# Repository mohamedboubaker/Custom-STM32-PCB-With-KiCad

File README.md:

# Custom STM32 PCB With KiCad
The design details are posted on EmbeddedProjects101.com: <a href="https://embeddedprojects101.com/custom-stm32-development-board/">Build a Custom STM32 PCB with KiCad</a>

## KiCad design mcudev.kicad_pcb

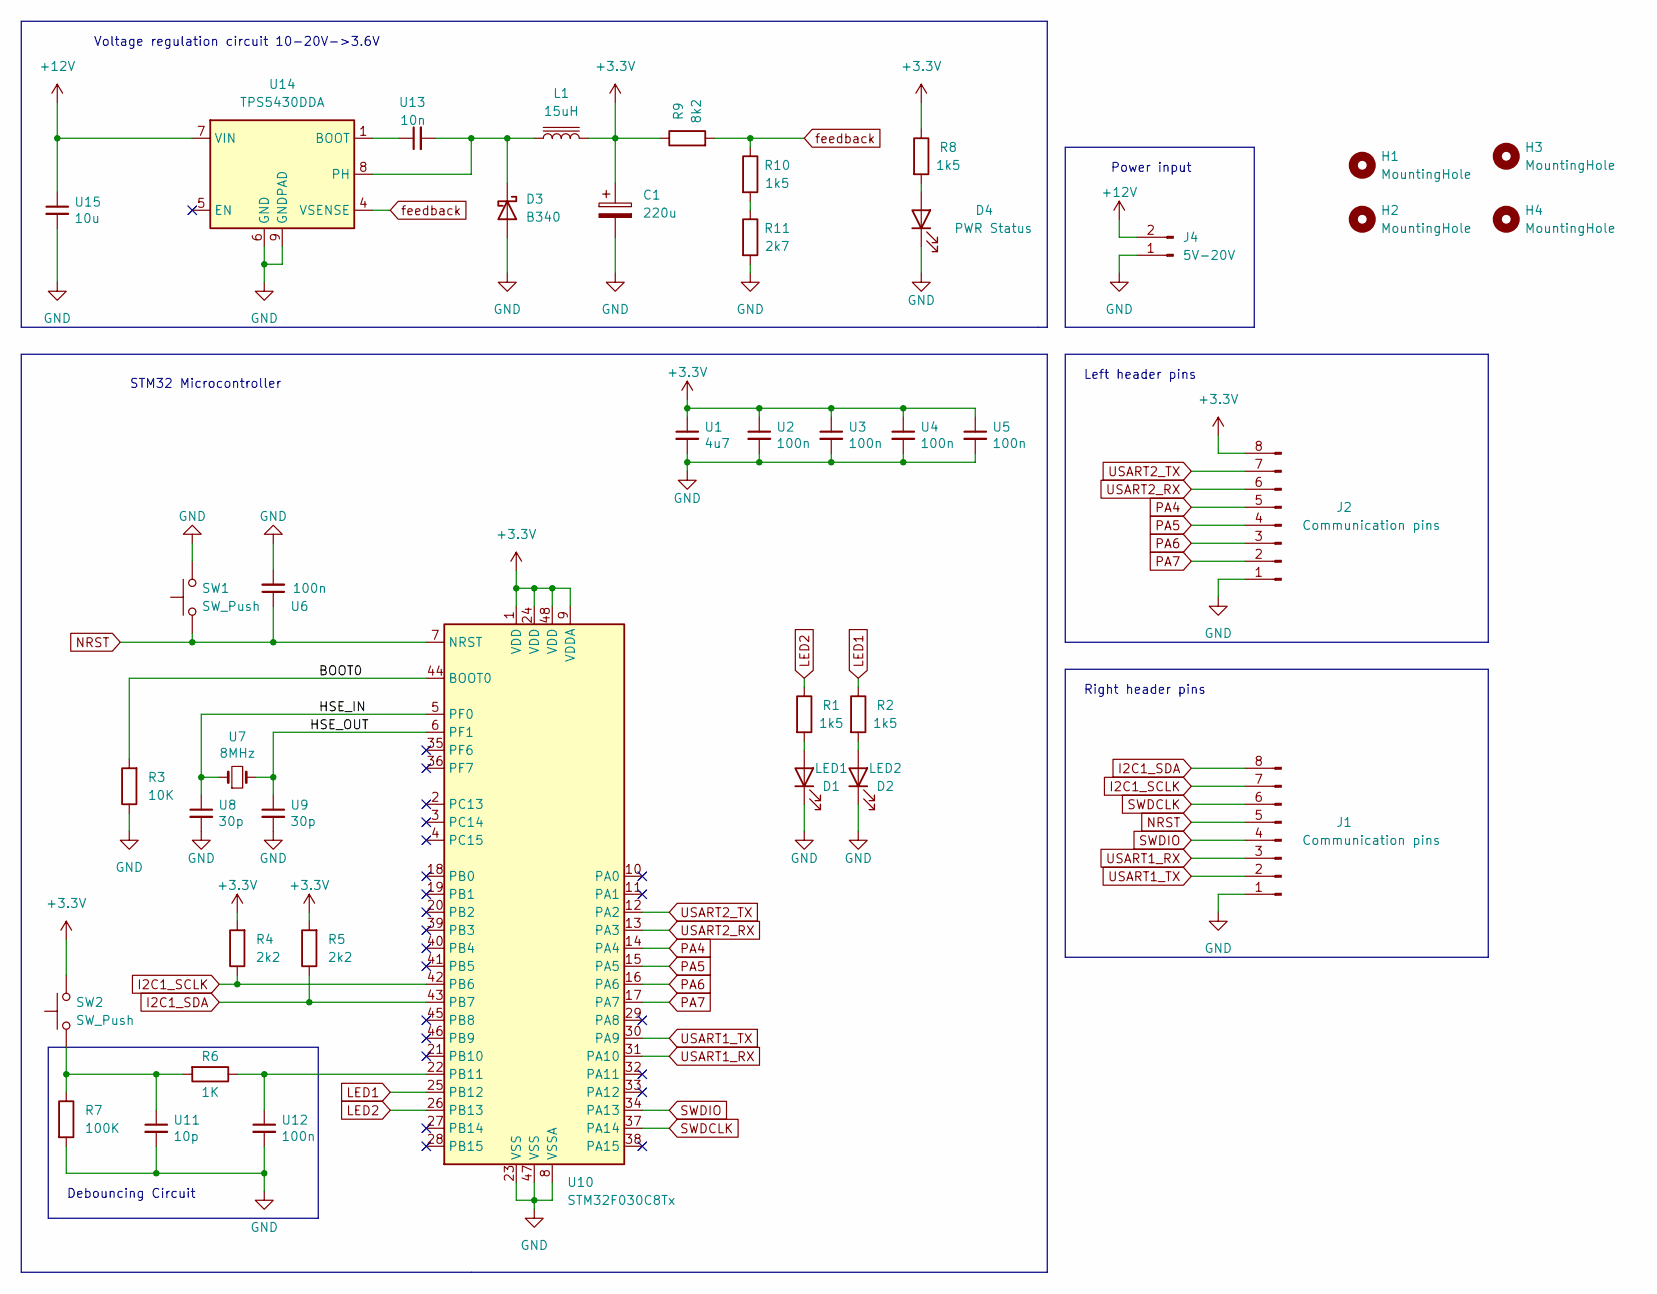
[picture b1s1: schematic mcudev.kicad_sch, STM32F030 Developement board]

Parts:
C1: 220u; CP_EIA-7343-15_Kemet-W; LCSC Part # C242173
D1: LED1; LED_0603_1608Metric; LCSC Part # C72043
D2: LED2; LED_0603_1608Metric; LCSC Part # C72041
D3: B340; D_SMA; LCSC Part # C64982
D4: PWR Status; LED_0603_1608Metric; LCSC Part # C2286
H1, H2, H3, H4: MountingHole; MountingHole_2.2mm_M2
J1, J2: Communication pins; PinHeader_1x08_P2.54mm_Vertical
J4: 5V-20V; PinHeader_1x02_P2.54mm_Vertical
L1: 15uH; L_10.4x10.4_H4.8; LCSC Part # C225048
R1, R2, R8: 1k5; R_0603_1608Metric; LCSC Part # C22843
R3: 10K; R_0402_1005Metric; LCSC Part # C25744
R4, R5: 2k2; R_0402_1005Metric; LCSC Part # C25879
R6: 1K; R_0603_1608Metric; LCSC Part # C21190
R7: 100K; R_0603_1608Metric; LCSC Part # C25803
R9: 8k2; R_0805_2012Metric; LCSC Part # C17828
R10: 1k5; R_0805_2012Metric; LCSC Part # C4310
R11: 2k7; R_0805_2012Metric; LCSC Part # C17530
SW1, SW2: SW_Push; SW_Push_1P1T_NO_CK_KSC6xxJ; LCSC Part # C318884
U1: 4u7; C_0603_1608Metric; LCSC Part # C19666
U2, U3, U4, U5, U6, U12: 100n; C_0402_1005Metric; LCSC Part # C1525
U7: 8MHz; Crystal_SMD_5032-2Pin_5.0x3.2mm; LCSC Part # C115962
U8, U9: 30p; C_0402_1005Metric; LCSC Part # C1570
U10: STM32F030C8Tx; LQFP-48_7x7mm_P0.5mm; LCSC Part # C23922
U11: 10p; C_0402_1005Metric; LCSC Part # C32949
U13: 10n; C_0805_2012Metric; LCSC Part # C1710
U14: TPS5430DDA; TI_SO-PowerPAD-8_ThermalVias; LCSC Part # C9864
U15: 10u; C_0805_2012Metric; LCSC Part # C15850

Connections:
+3.3V: C1.1, J2.8, L1.2, R4.2, R5.2, R8.1, R9.1, SW2.2, U1.1, U2.1, U3.1, U4.1, U5.1, U10.1 (VDD), U10.9 (VDDA), U10.24 (VDD), U10.48 (VDD)
+12V: J4.2, U14.7 (VIN), U15.1
/BOOT0: R3.2, U10.44 (BOOT0)
/HSE_IN: U7.1, U8.1, U10.5 (PF0)
/HSE_OUT: U7.2, U9.1, U10.6 (PF1)
GND: C1.2, D1.1 (K), D2.1 (K), D3.2 (A), D4.1 (K), J1.1, J2.1, J4.1, R3.1, R7.2, R11.2, SW1.2, U1.2, U2.2, U3.2, U4.2, U5.2, U6.2, U8.2, U9.2, U10.8 (VSSA), U10.23 (VSS), U10.47 (VSS), U11.2, U12.2, U14.6 (GND), U14.9 (GNDPAD), U15.2
I2C1_SCLK: J1.7, R4.1, U10.42 (PB6)
I2C1_SDA: J1.8, R5.1, U10.43 (PB7)
LED1: R2.1, U10.25 (PB12)
LED2: R1.1, U10.26 (PB13)
NRST: J1.5, SW1.1, U6.1, U10.7 (NRST)
unnamed: D1.2 (A), R1.2
unnamed: D2.2 (A), R2.2
unnamed: D3.1 (K), L1.1, U13.2, U14.8 (PH)
unnamed: D4.2 (A), R8.2
unnamed: R6.1, U10.22 (PB11), U12.1
unnamed: R6.2, R7.1, SW2.1, U11.1
unnamed: R10.2, R11.1
unnamed: U13.1, U14.1 (BOOT)
PA4: J2.5, U10.14 (PA4)
PA5: J2.4, U10.15 (PA5)
PA6: J2.3, U10.16 (PA6)
PA7: J2.2, U10.17 (PA7)
SWDCLK: J1.6, U10.37 (PA14)
SWDIO: J1.4, U10.34 (PA13)
USART1_RX: J1.3, U10.31 (PA10)
USART1_TX: J1.2, U10.30 (PA9)
USART2_RX: J2.6, U10.13 (PA3)
USART2_TX: J2.7, U10.12 (PA2)
feedback: R9.2, R10.1, U14.4 (VSENSE)

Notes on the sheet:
Power input
STM32 Microcontroller
Voltage regulation circuit 10-20V->3.6V
Right header pins
Debouncing Circuit
Left header pins

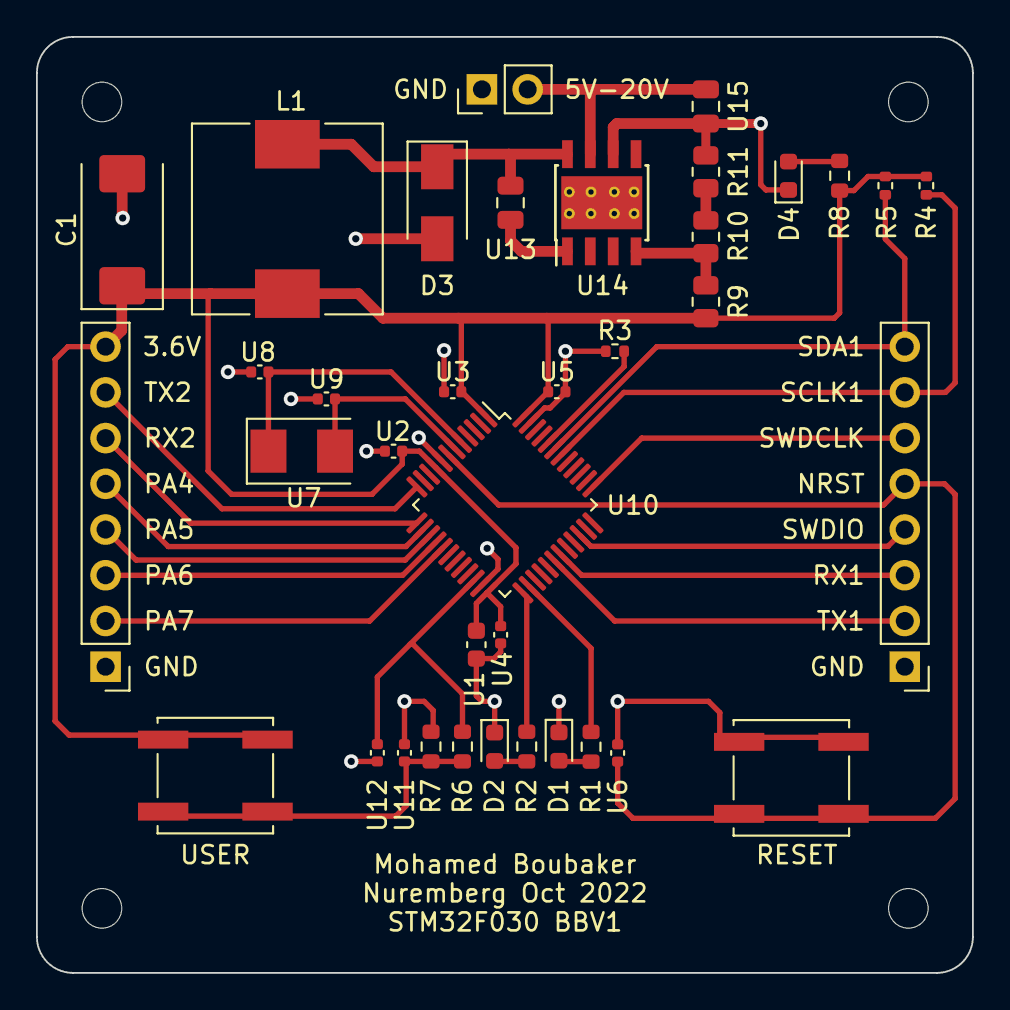
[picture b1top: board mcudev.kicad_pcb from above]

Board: 2 copper layers, 52.0 x 52.0 mm, 41 parts (0 on the bottom side), 30 nets.

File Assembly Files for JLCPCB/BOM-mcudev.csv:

Comment,Designator,Footprint,LCSC
"220u","C1","Capacitor_Tantalum_SMD:CP_EIA-7343-15_Kemet-W","C242173"
"LED1","D1","LED_SMD:LED_0603_1608Metric","C72043"
"LED2","D2","LED_SMD:LED_0603_1608Metric","C72041"
"B340","D3","Diode_SMD:D_SMA","C64982"
"PWR Status","D4","LED_SMD:LED_0603_1608Metric","C2286"
"MountingHole","H1,H2,H3,H4","MountingHole:MountingHole_2.2mm_M2",""
"Communication pins","J1,J2","Connector_PinHeader_2.54mm:PinHeader_1x08_P2.54mm_Vertical",""
"5V-20V","J4","Connector_PinHeader_2.54mm:PinHeader_1x02_P2.54mm_Vertical",""
"15uH","L1","Inductor_SMD:L_10.4x10.4_H4.8","C225048"
"1k5","R1,R2,R8","Resistor_SMD:R_0603_1608Metric","C22843"
"1k5","R10","Resistor_SMD:R_0805_2012Metric","C4310"
"2k7","R11","Resistor_SMD:R_0805_2012Metric","C17530"
"10K","R3","Resistor_SMD:R_0402_1005Metric","C25744"
"2k2","R4,R5","Resistor_SMD:R_0402_1005Metric","C25879"
"1K","R6","Resistor_SMD:R_0603_1608Metric","C21190"
"100K","R7","Resistor_SMD:R_0603_1608Metric","C25803"
"8k2","R9","Resistor_SMD:R_0805_2012Metric","C17828"
"SW_Push","SW1,SW2","Button_Switch_SMD:SW_Push_1P1T_NO_CK_KSC6xxJ","C318884"
"4u7","U1","Capacitor_SMD:C_0603_1608Metric","C19666"
"STM32F030C8Tx","U10","Package_QFP:LQFP-48_7x7mm_P0.5mm","C23922"
"10p","U11","Capacitor_SMD:C_0402_1005Metric","C32949"
"10n","U13","Capacitor_SMD:C_0805_2012Metric","C1710"
"TPS5430DDA","U14","Package_SO:TI_SO-PowerPAD-8_ThermalVias","C9864"
"10u","U15","Capacitor_SMD:C_0805_2012Metric","C15850"
"100n","U2,U3,U4,U5,U6,U12","Capacitor_SMD:C_0402_1005Metric","C1525"
"8MHz","U7","Crystal:Crystal_SMD_5032-2Pin_5.0x3.2mm","C115962"
"30p","U8,U9","Capacitor_SMD:C_0402_1005Metric","C1570"

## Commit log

2023-10-17 added PCB picture
2023-10-17 added PCB GIF
